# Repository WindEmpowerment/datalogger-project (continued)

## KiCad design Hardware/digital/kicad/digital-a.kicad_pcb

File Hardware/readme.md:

# HARDWARE ORGANISATION
Here are hardware's files for the windlogger project.

## BLOCK DIAGRAM

Green : it's working
Yellow : Work in progress
Red : Need to be implement

The differents signals from the sensors are adapted on the shield board to be accepted by the micro controller (between 0 and 5V).
All data are timestamped at each measure and can be save on the SD card or transmit on a serial interface.
Transmitter like the ESP-01 or ESP-12 wifi module can be use like a serial to wifi converter to send data on the web.
Transmitter like M590E or A gprs module, with a sim card, can be use like a serial to gprs converter.

Work is under development and lot's of function need to be implemented.

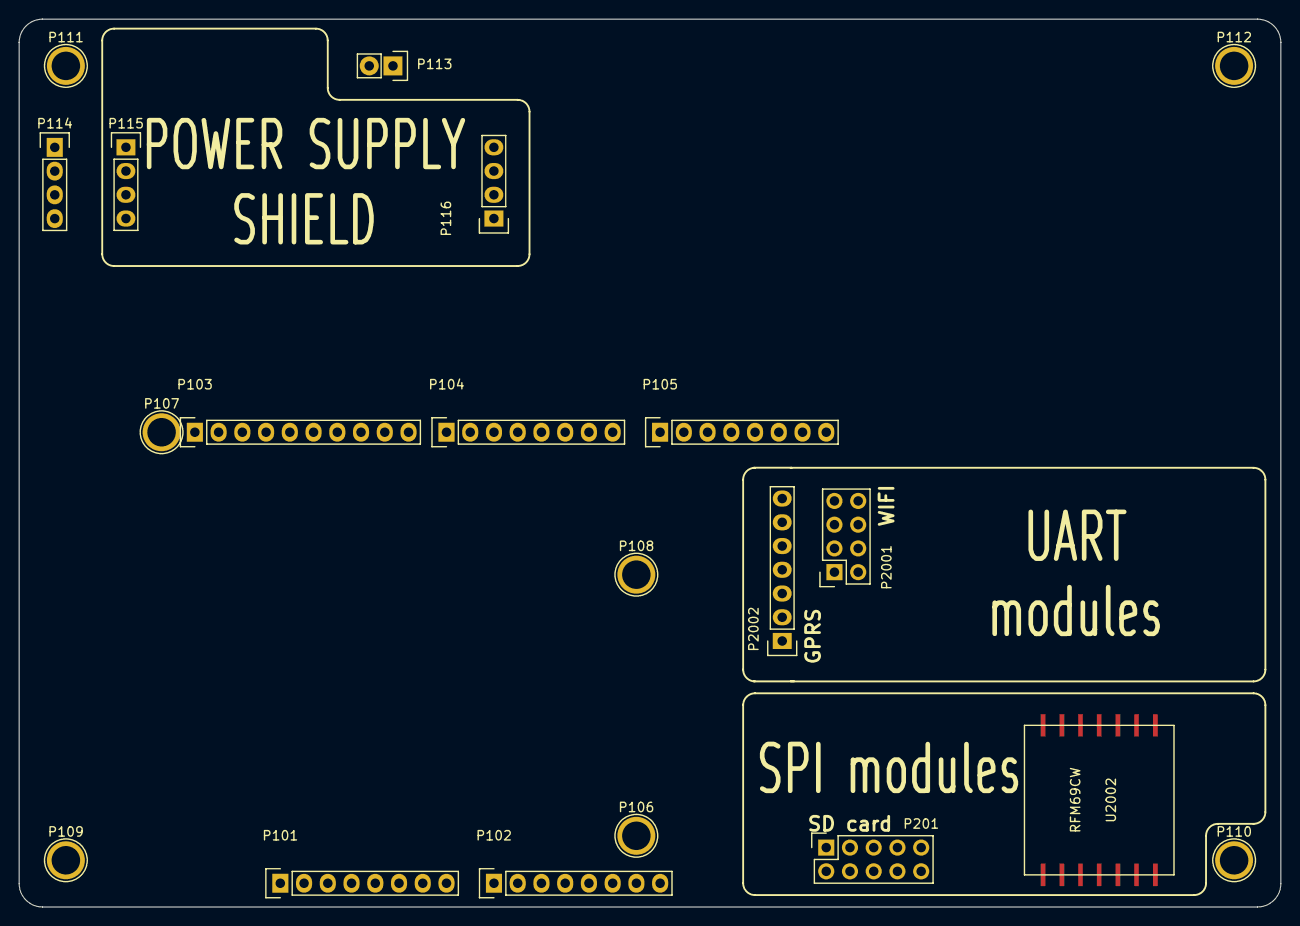
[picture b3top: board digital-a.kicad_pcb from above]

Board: 2 copper layers, 135.0 x 95.0 mm, 20 parts (0 on the bottom side), 9 nets, no tracks yet.

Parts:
P101: Power; Socket_Strip_Straight_1x08
P102: Analog; Socket_Strip_Straight_1x08
P103: PWM; Socket_Strip_Straight_1x10
P104: PWM; Socket_Strip_Straight_1x08
P105: Communication; Socket_Strip_Straight_1x08
P106: h2; Arduino_1pin
P107: h3; Arduino_1pin
P108: h4; Arduino_1pin
P109: h5; Arduino_1pin
P110: h6; Arduino_1pin
P111: h7; Arduino_1pin
P112: h8; Arduino_1pin
P113: 5VDC; Socket_Strip_Straight_1x02
P114: POWER_SOURCE; Socket_Strip_Straight_1x04
P115, P116: CONN_01X04; Socket_Strip_Straight_1x04
P201: SD CARD; Socket_Strip_Straight_2x05
P2001: WIFI; Socket_Strip_Straight_2x04
P2002: GPRS; Socket_Strip_Straight_1x07
U2002: RFM69CW

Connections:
+5V: P113.2, P116.4
/F1_output-a/MISO: P103.6, P201.8, U2002.8
/F1_output-a/MOSI: P103.7, P201.3, U2002.5
/F1_output-a/SCLK: P103.5, P201.9, U2002.6
GND: P101.6, P101.7, P103.4, P113.1, P116.1, P116.3, P201.5, P201.10, U2002.3, U2002.14
unnamed: P114.1, P115.1
unnamed: P114.2, P115.2
unnamed: P114.3, P115.3
unnamed: P114.4, P115.4

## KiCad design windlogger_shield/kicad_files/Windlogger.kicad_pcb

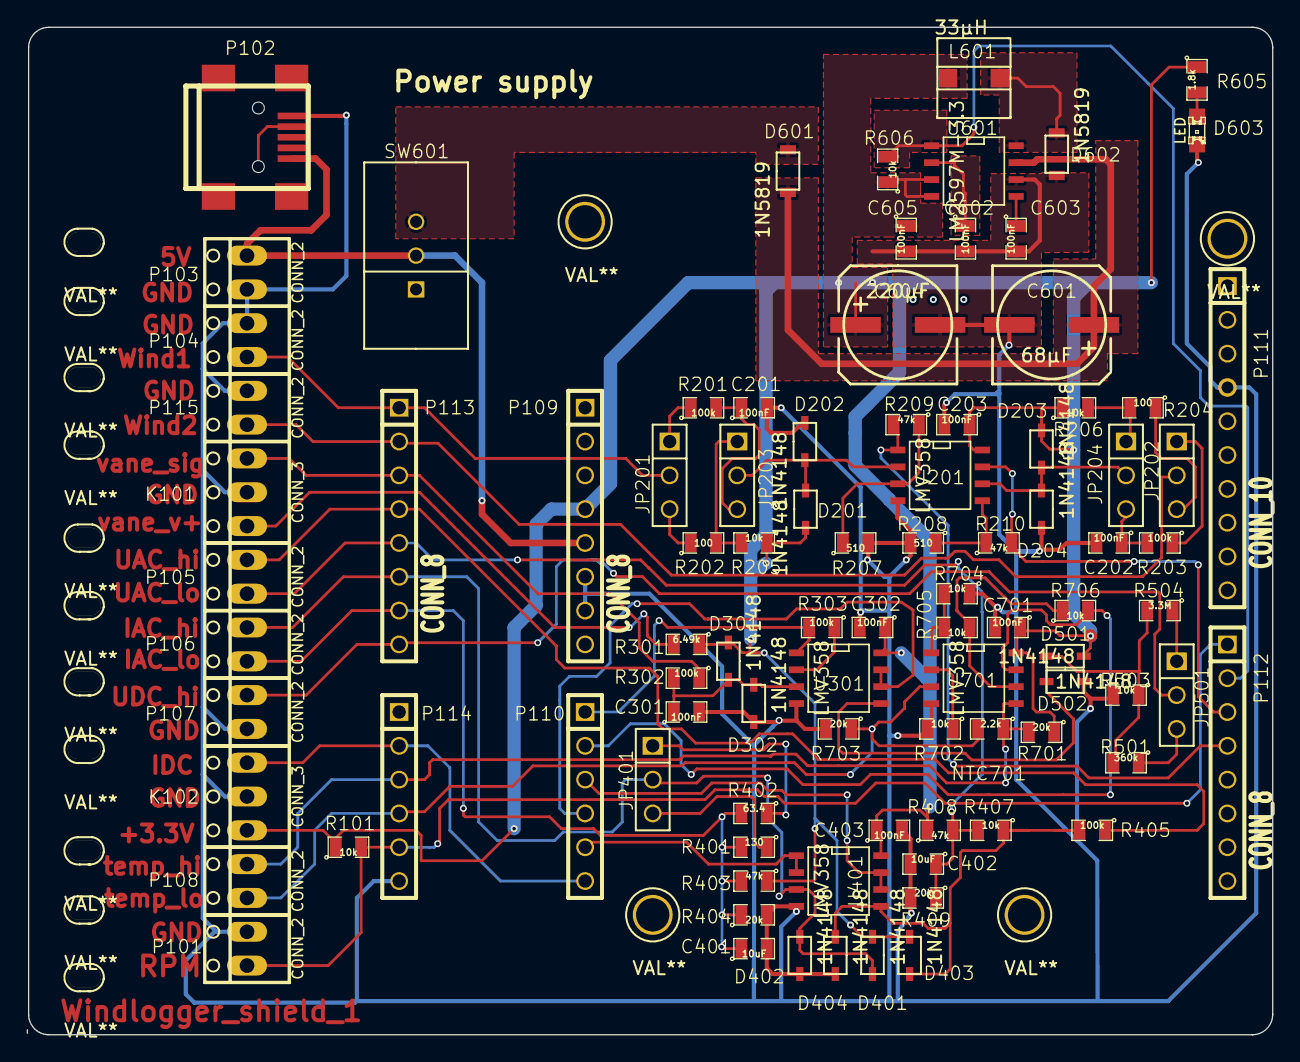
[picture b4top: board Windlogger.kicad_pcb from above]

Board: 2 copper layers, 93.5 x 75.7 mm, 93 parts (0 on the bottom side), 53 nets.

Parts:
C201, C202, C203, C301, C302, C403, C602, C603, C605, C701: 100nF; SM0805
C401, C402: 10uF; SM0805
C601: 68µF; SMDHD_VF
C604: 220µF; SMDHD_VF
D201, D202, D203, D204, D301, D302, D401, D402, D403, D404, D501, D502: 1N4148; SOD-323
D601, D602: 1N5819; SOD-123
D603: LED; LED-0805
JP201, JP202, JP203, JP204, JP401, JP501: JUMPER3; PIN_ARRAY_3X1_Windlogger
K101, K102: CONN_3; PINHEAD1-3_Windlogger
L601: 33µH; Bobine_cms
NTC701: 2.2k; SM0805
P101, P103, P104, P105, P106, P107, P108, P115: CONN_2; PINHEAD1-2_Windlogger
P102: CONN_5; USB_MINI_B
P109, P112, P113: CONN_8; SIL-8_Windlogger
P110, P114: CONN_6; SIL-6_Winlogger
P111: CONN_10; SIL-10_Winlogger
R101, R205, R206, R407, R503, R606, R702, R704, R705, R706: 10k; SM0805
R201, R203, R302, R303, R405: 100k; SM0805
R202, R204: 100; SM0805
R207, R208: 510; SM0805
R209, R210, R403, R408: 47k; SM0805
R301: 6.49k; SM0805
R401: 130; SM0805
R402: 63.4; SM0805
R404, R409, R701, R703: 20k; SM0805
R501: 360k; SM0805
R504: 3.3M; SM0805
R605: 1.8k; SM0805
SW601: SWITCH_INV; SWITCH_SPDT_Windlogger
U201, U301, U401, U701: LMV358; SO8N
U601: LM2597M-3.3; SO8N

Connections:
+3.3V: C203.1, C302.1, C403.1, C604.1, C605.1, C701.1, D201.2, D203.2, D301.2, D401.2, D403.2, D501.2, K102.1, L601.2, P109.4, R101.1, R205.1, R206.1, R301.1, R403.1, R408.1, R605.1, R606.1, R701.1, U201.8, U301.8, U401.8, U601.3, U601.4, U701.8
/F1 Anemometre/Speed1: P112.4, R209.2, U201.1
/F1 Anemometre/Speed2: P112.3, R210.2, U201.7
/F1 Anemometre/Wind1: JP201.2, P104.1, P113.1
/F1 Anemometre/Wind2: JP202.2, P113.2, P115.1
/F2 Girouette/Udir: P110.1, R303.2, U301.1
/F2 Girouette/vane_sig: K101.3, P113.3, R302.1
/F2 Girouette/vane_v+: K101.1, R301.2
/F3 Wattmetre_AC/0-16A: JP401.3, R401.1
/F3 Wattmetre_AC/0-32A: JP401.1, R402.1
/F3 Wattmetre_AC/IAC: P110.5, U401.1, U401.2
/F3 Wattmetre_AC/IAC_hi: D401.1, D402.2, JP401.2, P106.2, P113.6, U401.3
/F3 Wattmetre_AC/IAC_lo: C401.1, P106.1, P113.7, R401.2, R402.2, R403.2, R404.1
/F3 Wattmetre_AC/UAC_hi: P105.2, P113.4, R405.1
/F3 Wattmetre_AC/UAC_lo: C402.1, P105.1, P113.5, R407.2, R408.2, R409.1
/F3 Wattmetre_AC/Ugrid: P110.3, U401.6, U401.7
/F4 Wattmetre_DC/64V: JP501.3, R501.1
/F4 Wattmetre_DC/640V: JP501.1, R504.1
/F4 Wattmetre_DC/UDC_hi: JP501.2, P107.2, P113.8
/F4 Wattmetre_DC/Ubat: P110.4, U301.6, U301.7
/F5 Temperature/Utemp: P110.2, R706.2, U701.7
/F5 Temperature/temp_hi: NTC701.1, P108.2, P114.3, R701.2, U701.5
/F5 Temperature/temp_lo: NTC701.2, P108.1, P114.4, R703.1, U701.3
/F6 Alimentation/5V: P102.5, P103.2, P109.5, SW601.2
/F6 Alimentation/5v_sw: D601.1, SW601.3
/F6 Alimentation/Power_fail: P112.2, R606.2, U601.1
/F6 Alimentation/vin_lm2597: C601.1, D601.2, U601.7
/F6 Alimentation/vs1: D602.2, L601.1, U601.8
/IDC: K102.3, P110.6, P114.2
/RPM: P101.1, P112.1, P114.5, R101.2
AGND: C201.2, C202.2, C203.2, C301.2, C302.2, C401.2, C402.2, C403.2, C601.2, C602.2, C603.2, C604.2, C605.2, C701.2, D202.1, D204.1, D302.1, D402.1, D404.1, D502.1, D602.1, D603.2, K101.2, K102.2, P101.2, P102.1, P103.1, P104.2, P107.1, P109.6, P109.7, P111.4, P114.6, P115.2, R207.2, R208.2, R404.2, R409.2, R503.2, R702.2, R703.2, R704.1, U201.4, U301.4, U401.4, U601.6, U701.4
unnamed: C201.1, JP203.3, R201.2
unnamed: C202.1, JP204.3, R203.2
unnamed: C301.1, D301.1, D302.2, R302.2, U301.3
unnamed: C602.1, U601.2
unnamed: C603.1, U601.5
unnamed: D201.1, D202.2, JP203.2, U201.2
unnamed: D203.1, D204.2, JP204.2, U201.6
unnamed: D403.1, D404.2, R405.2, R407.1, U401.5
unnamed: D501.1, D502.2, R501.2, R503.1, R504.2, U301.5
unnamed: D603.1, R605.2
unnamed: JP201.1, R201.1
unnamed: JP201.3, R202.1
unnamed: JP202.1, R203.1
unnamed: JP202.3, R204.1
unnamed: JP203.1, R202.2, R205.2
unnamed: JP204.1, R204.2, R206.2
unnamed: R207.1, R209.1, U201.3
unnamed: R208.1, R210.1, U201.5
unnamed: R303.1, U301.2
unnamed: R702.1, U701.2
unnamed: R704.2, R705.1, U701.1
unnamed: R705.2, R706.1, U701.6

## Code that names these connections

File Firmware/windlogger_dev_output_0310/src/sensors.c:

/**
 * @file   sensors.c
 * @author gilou
 * @date   30 août 2016
 * @brief  Brief description of file.
 *
 * Detailed description of file.
 */

#include <avr/interrupt.h>
#include "../lib/main.h"
#include "../lib/sensors.h"



void measure_clear(Measure *_measure)
{
	_measure->speed1 = 0;
	_measure->speed2 = 0;
	_measure->degree = 0;
	_measure->acPower = 0;
	_measure->dcPower = 0;
	_measure->temp = 0;
	_measure->rpm = 0;
}

void anemos_init(void)
{

}

void anemo_start_count(void)
{



}

void anemo_read_value(Measure *_measure)
{

}



void dir_value(Measure *_measure)
{

}

void temp_value(Measure *_measure)
{

}

float inst_AC_voltage()
{

	return 0;
}

float inst_AC_current()
{

	return 0;
}

float AC_voltage_offset()
{

return 0;
}

float AC_current_offset()
{

return 0;
}

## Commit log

2015-04-23 Create test
2015-04-23 Update test
2015-04-23 j'ai mis Ok for Jay
2015-04-23 test yasin
2015-12-12 Add windlogger shield prosition's files
2015-12-12 README.md
2016-03-10 Add files
2016-10-13 some change in README.md
2016-10-16 add kicad files
2016-10-16 update kicad files
2016-10-16 add shield_preview.jpg
2016-10-22 add diagram.svg
2016-10-22 upload diagram.png
2016-10-29 update digital files
2016-10-29 add diagram.png
2016-10-29 add firmware's files
2016-11-02 remove wrong files
2016-11-02 add my windturbine files
2017-01-25 update files
2017-02-02 move to digital v1.0.1
2017-04-10 move to digital 1.1.1
2017-04-11 clean firmware/
2017-04-11 add /shield/Documents folder
2017-04-20 add comment
